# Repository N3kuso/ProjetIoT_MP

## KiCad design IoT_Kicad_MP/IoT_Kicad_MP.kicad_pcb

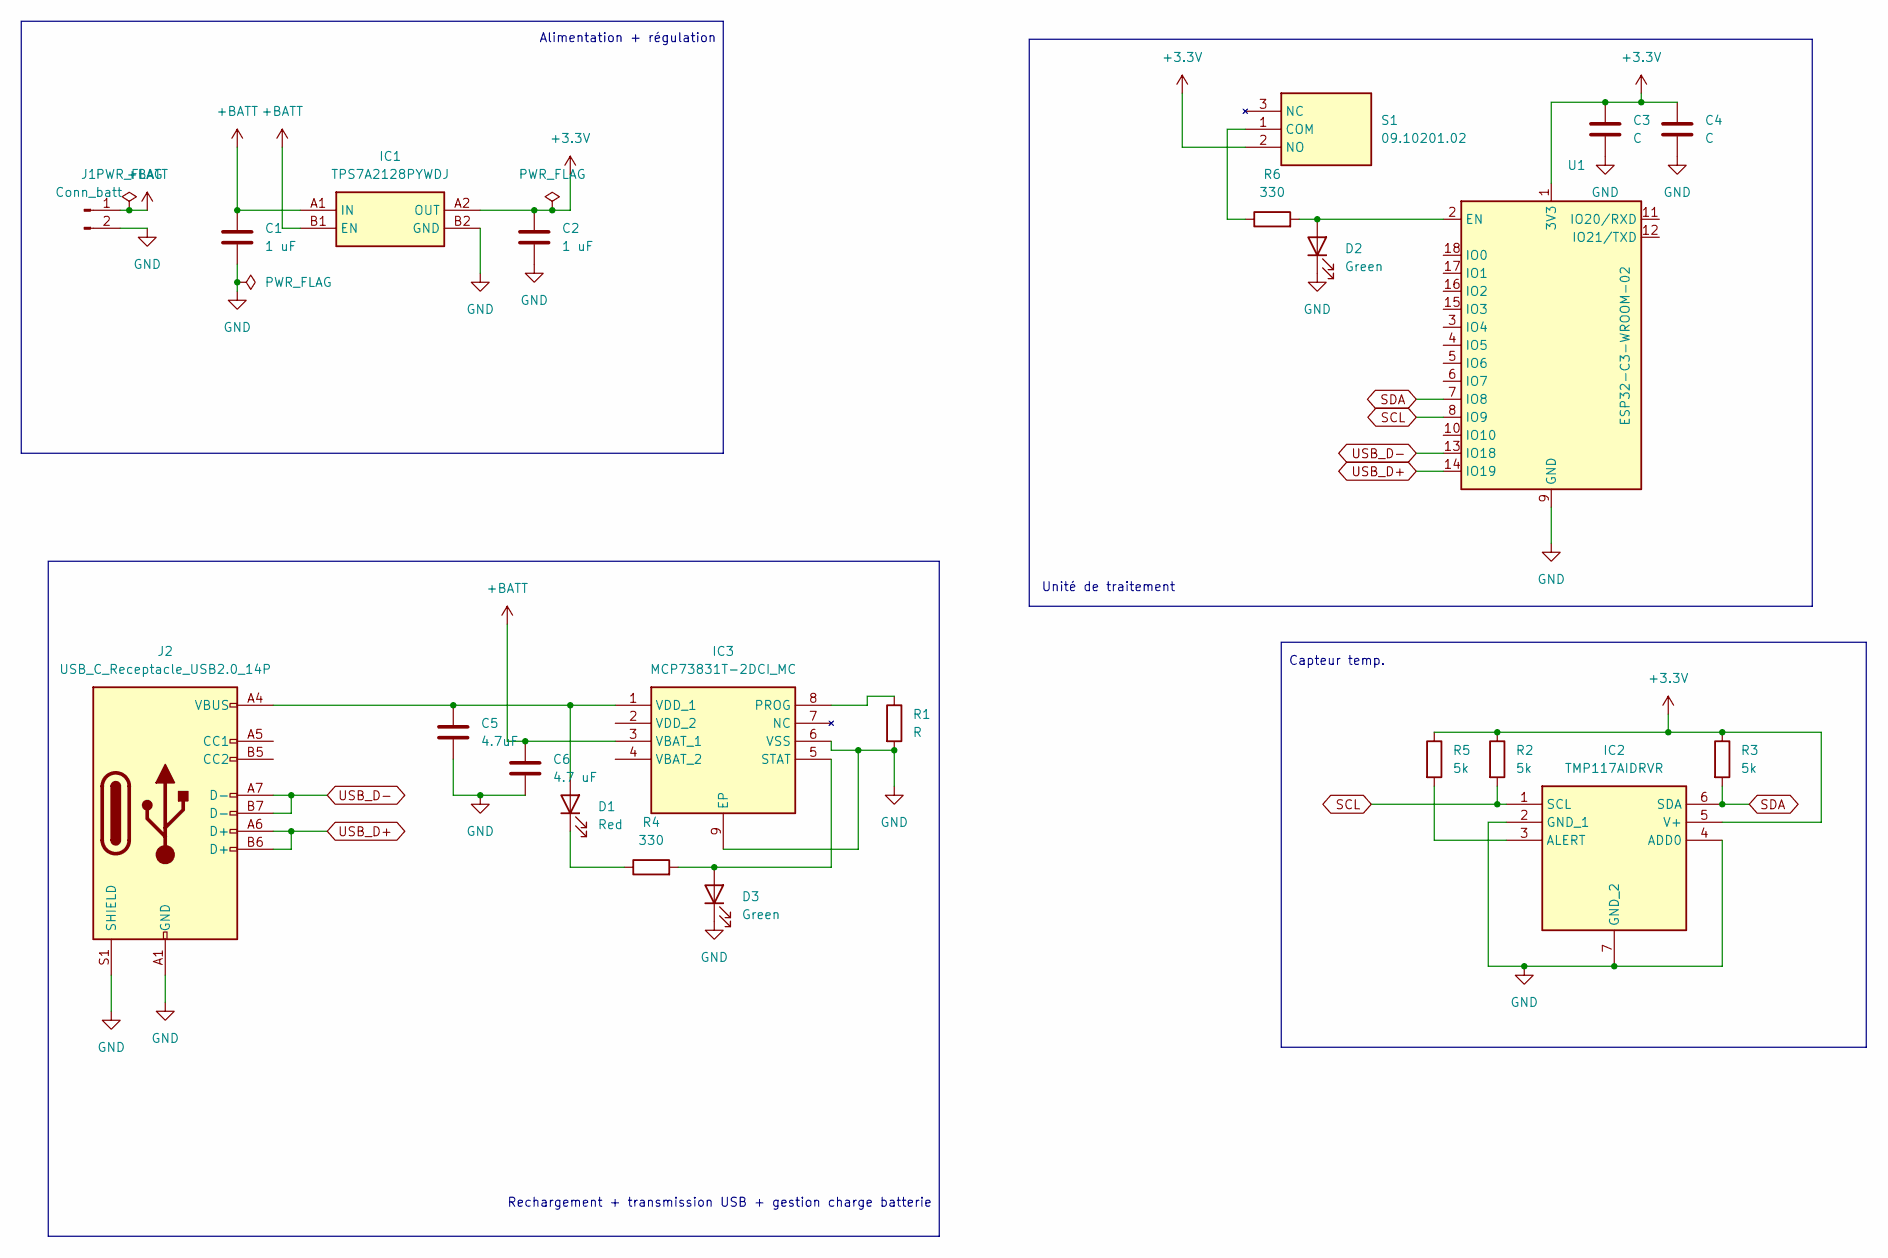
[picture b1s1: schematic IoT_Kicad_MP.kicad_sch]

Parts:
C1, C2: 1 uF; C_0805_2012Metric
C3, C4: C; C_0805_2012Metric
C5: 4.7uF; C_0805_2012Metric
C6: 4.7 uF; C_0805_2012Metric
D1: Red; LED_0805_2012Metric
D2, D3: Green; LED_0805_2012Metric
IC1: TPS7A2128PYWDJ; Manufacturer_Part_Number TPS7A2128PYWDJ; Mouser Part Number 595-TPS7A2128PYWDJ
IC2: TMP117AIDRVR; SON65P200X200X80-7N; Manufacturer_Part_Number TMP117AIDRVR; Mouser Part Number 595-TMP117AIDRVR
IC3: MCP73831T-2DCI_MC; SON50P300X200X100-9N-D; Manufacturer_Part_Number MCP73831T-2DCI/MC; Mouser Part Number 579-MCP73831T-2DCIMC
J1: Conn_batt; SolderWire-0.1sqmm_1x02_P3.6mm_D0.4mm_OD1mm
J2: USB_C_Receptacle_USB2.0_14P; USB_C_Receptacle_JAE_DX07S016JA1R1500
R1: R; R_0805_2012Metric
R2, R3, R5: 5k; R_0805_2012Metric
R4, R6: 330; R_0805_2012Metric
S1: 09.10201.02; 091020102; Manufacturer_Part_Number 09.10201.02; Mouser Part Number 123-09.10201.02
U1: ESP32-C3-WROOM-02

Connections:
+3.3V: C2.1, C3.1, C4.1, IC1.A2 (OUT), IC2.5 (V+), R2.1, R3.1, R5.1, S1.2 (NO), U1.1 (3V3)
+BATT: C1.1, C6.1, IC1.A1 (IN), IC1.B1 (EN), IC3.3 (VBAT_1), J1.1
GND: C1.2, C2.2, C3.2, C4.2, C5.2, C6.2, D2.1 (K), D3.1 (K), IC1.B2 (GND), IC2.2 (GND_1), IC2.4 (ADD0), IC2.7 (GND_2), IC3.6 (VSS), IC3.9 (EP), J1.2, J2.A1 (GND), J2.A12 (GND), J2.B1 (GND), J2.B12 (GND), J2.S1 (SHIELD), R1.2, U1.9 (GND), U1.19 (GND)
unnamed: C5.1, D1.2 (A), IC3.1 (VDD_1), J2.A4 (VBUS), J2.A9 (VBUS), J2.B4 (VBUS), J2.B9 (VBUS)
unnamed: D1.1 (K), R4.1
unnamed: D2.2 (A), R6.2, U1.2 (EN)
unnamed: D3.2 (A), IC3.5 (STAT), R4.2
unnamed: IC2.3 (ALERT), R5.2
unnamed: IC3.8 (PROG), R1.1
unnamed: R6.1, S1.1 (COM)
SCL: IC2.1 (SCL), R2.2, U1.8 (IO9)
SDA: IC2.6 (SDA), R3.2, U1.7 (IO8)
USB_D+: J2.A6 (D+), J2.B6 (D+), U1.14 (IO19)
USB_D-: J2.A7 (D-), J2.B7 (D-), U1.13 (IO18)

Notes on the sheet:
Alimentation + régulation
Rechargement + transmission USB + gestion charge batterie
Capteur temp.
Unité de traitement

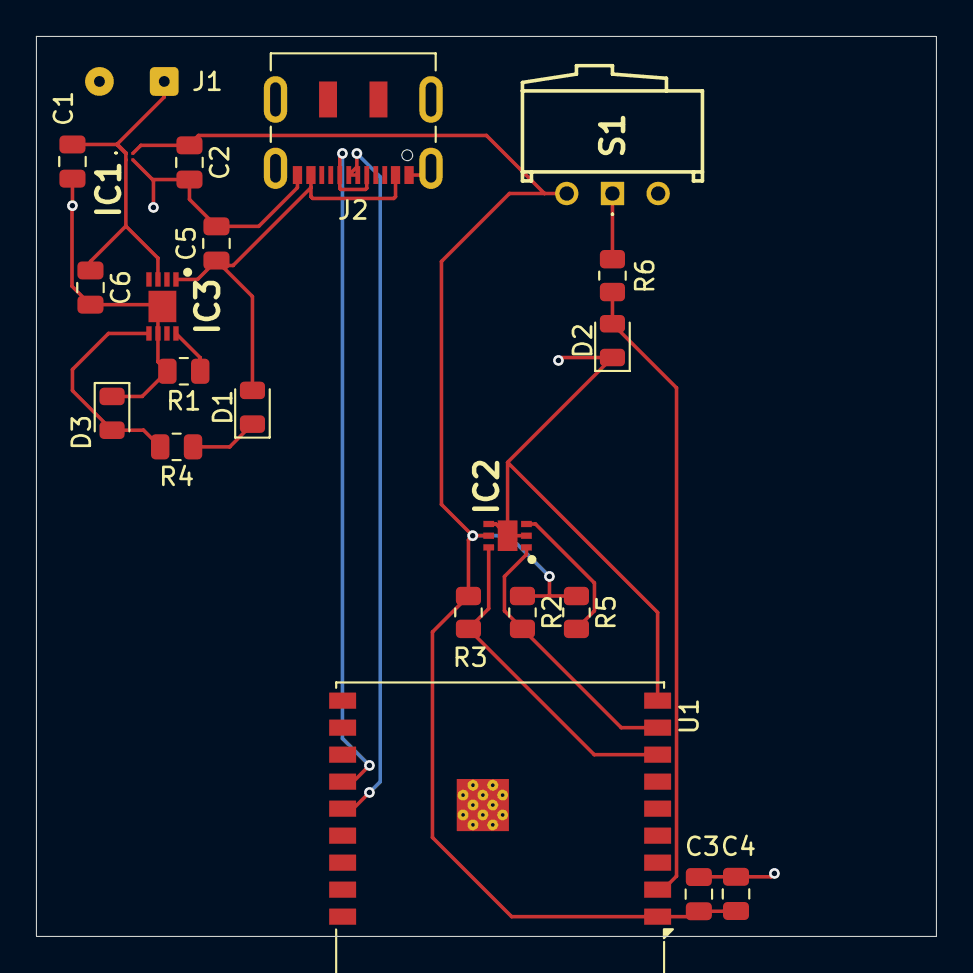
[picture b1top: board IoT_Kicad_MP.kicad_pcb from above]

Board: 2 copper layers, 50.0 x 50.0 mm, 22 parts (0 on the bottom side), 14 nets.

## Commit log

2024-10-24 Fichier schéma + routage
2024-10-24 Ajout calcul batterie
